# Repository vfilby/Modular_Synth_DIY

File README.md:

# Modular_Synth_DIY

Landing page from some audio DIY projects.  This is a work in progress and the circuits/PCBs currently available are untested and should not be used at this point unless you are very brave and assume all responsibility for your own actions.

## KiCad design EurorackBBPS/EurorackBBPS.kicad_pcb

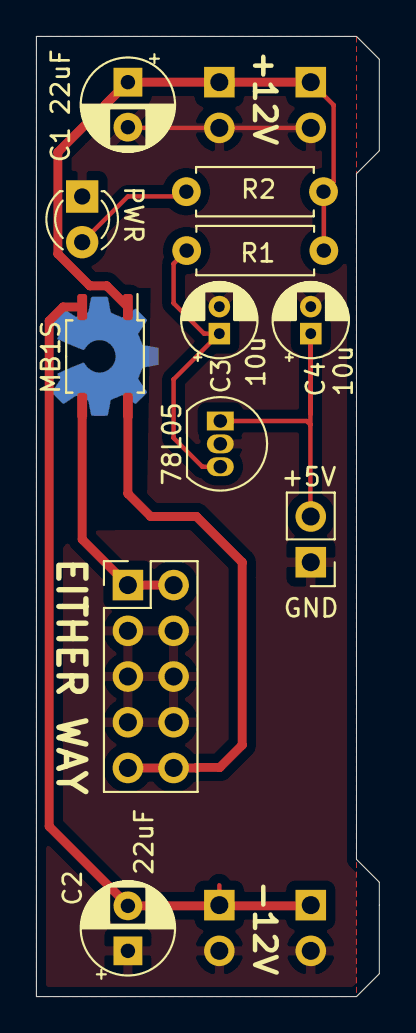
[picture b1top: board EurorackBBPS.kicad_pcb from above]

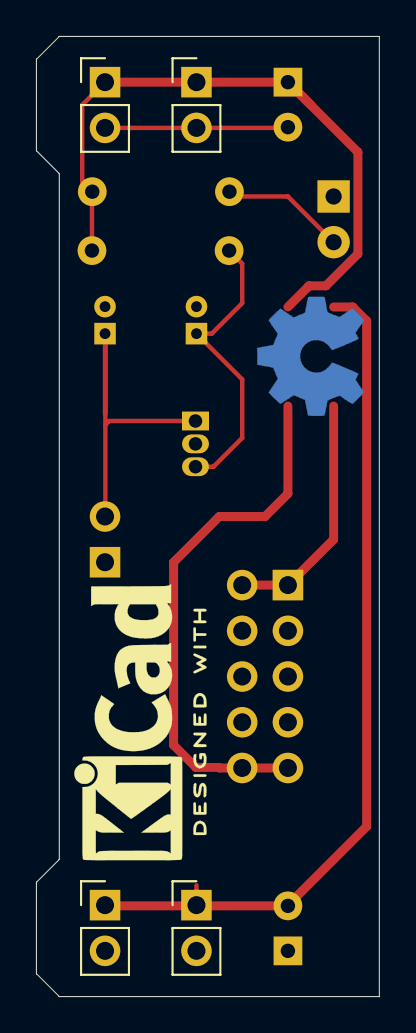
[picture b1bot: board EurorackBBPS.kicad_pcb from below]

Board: 2 copper layers, 19.1 x 53.3 mm, 15 parts (4 on the bottom side), 8 nets.

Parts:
78L05: L78L05_TO92; TO-92_Inline
C1, C2: 22uF; CP_Radial_D5.0mm_P2.50mm
C3, C4: 10u; CP_Radial_D4.0mm_P1.50mm
GND: Conn_01x02_Male; PinHeader_1x02_P2.54mm_Vertical
J1: SV1; PinHeader_2x05_P2.54mm_Vertical
J2: +12V Rail 1; PinHeader_1x02_P2.54mm_Vertical
J3: +12V Rail 2; PinHeader_1x02_P2.54mm_Vertical
J4: -12V Rail 1; PinHeader_1x02_P2.54mm_Vertical
J5: -12V Rail 2; PinHeader_1x02_P2.54mm_Vertical
MB1S: MB1S; SOP-4_3.8x4.1mm_P2.54mm
PWR: LED; LED_D3.0mm
R1: 4.7R; R_Axial_DIN0207_L6.3mm_D2.5mm_P7.62mm_Horizontal
R2: 330R; R_Axial_DIN0207_L6.3mm_D2.5mm_P7.62mm_Horizontal

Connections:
+5V: 78L05.1, C4.1, GND.2
+12V: C1.1, J2.1, J3.1, MB1S.1, R1.2, R2.2
-12V: C2.2, J4.1, J5.1, MB1S.2
GND: 78L05.2, C1.2, C2.1, C3.2, C4.2, GND.1, J1.3, J1.4, J1.5, J1.6, J1.7, J1.8, J2.2, J3.2, J4.2, J5.2, PWR.1
unnamed: J1.1, J1.2, MB1S.3
unnamed: J1.9, J1.10, MB1S.4
unnamed: 78L05.3, C3.1, R1.1
unnamed: PWR.2, R2.1

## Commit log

2021-06-09 Adding .gitignore
2021-06-09 Adding basic eurorack -> breadboard adapter. This is completely untested at this point. Do not use.
